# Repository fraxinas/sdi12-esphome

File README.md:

# SDI-12 Interface for ESPHome

(CC) 2023 by Andreas Frisch <github@fraxinas.dev>

## OwO what's this?
**`sdi12-esphome` is an ESP32-based interface for connecting professional meteorologic sensors with ESPHome and Home Assistant**

## Hardware Features
* Based on a NodeMCU ESP32 Module
* 4x SDI-12 inputs via push-in terminals
* Step-up conversion for the 12V SDI-12 sensor power
* Transient surge protection for the SDI-12 data bus
* PCB fits into a BOPLA 100x100mm IP65 case

## Software Features
* Home Assistant intergration using ESPHome.io

## Custom Components
### SDI-12 Bus
* is a wrapper around the https://github.com/EnviroDIY/Arduino-SDI-12 library, with the https://github.com/RAKWireless/RAK13010-SDI12/ modifications to split input, output and enable into separate GPIOs
* allows configuring an SDI-12 Bus component that sensors can be attached to
* configure RX, TX & OE pins through configuration YAML
* provide address scan method

### CS215
* Campbell Scientific CS215 Temperature and Relative Humidity Probe
* https://s.campbellsci.com/documents/ca/manuals/cs215_man.pdf

### DS2
* Decagon Devices DS-2 Sonic Anemometer
* https://library.metergroup.com/Manuals/14586_DS2_Web.pdf
* Sensors for
  * wind speed
  * wind direction
  * wind temperature

### TODOs
- [ ] SDI-12 Bus component (feature complete & tests)
- [ ] Themometer/Hygrometer (feature complete & tests)
- [ ] Anemometer (feature complete & tests)
- [ ] Rain Gauge (start)
- [ ] Generic Sensor (start)
- [ ] Documentation / Photos

## Project Diary
| Date       | Version | Milestone                                        |
| :--------- | :------ | :----------------------------------------------- |
| 2023-10-22 |         | Started Project on the breadboard                |
| 2023-11-06 |         | First successful sensor readout in EPSHome       |
| 2023-11-13 |  v0.1   | Order prototype design at JLCPCB                 |

## Resources
* https://www.sdi-12.org/current_specification/SDI-12_version-1_4-Jan-10-2019.pdf
* https://ww1.microchip.com/downloads/en/DeviceDoc/20005315B.pdf

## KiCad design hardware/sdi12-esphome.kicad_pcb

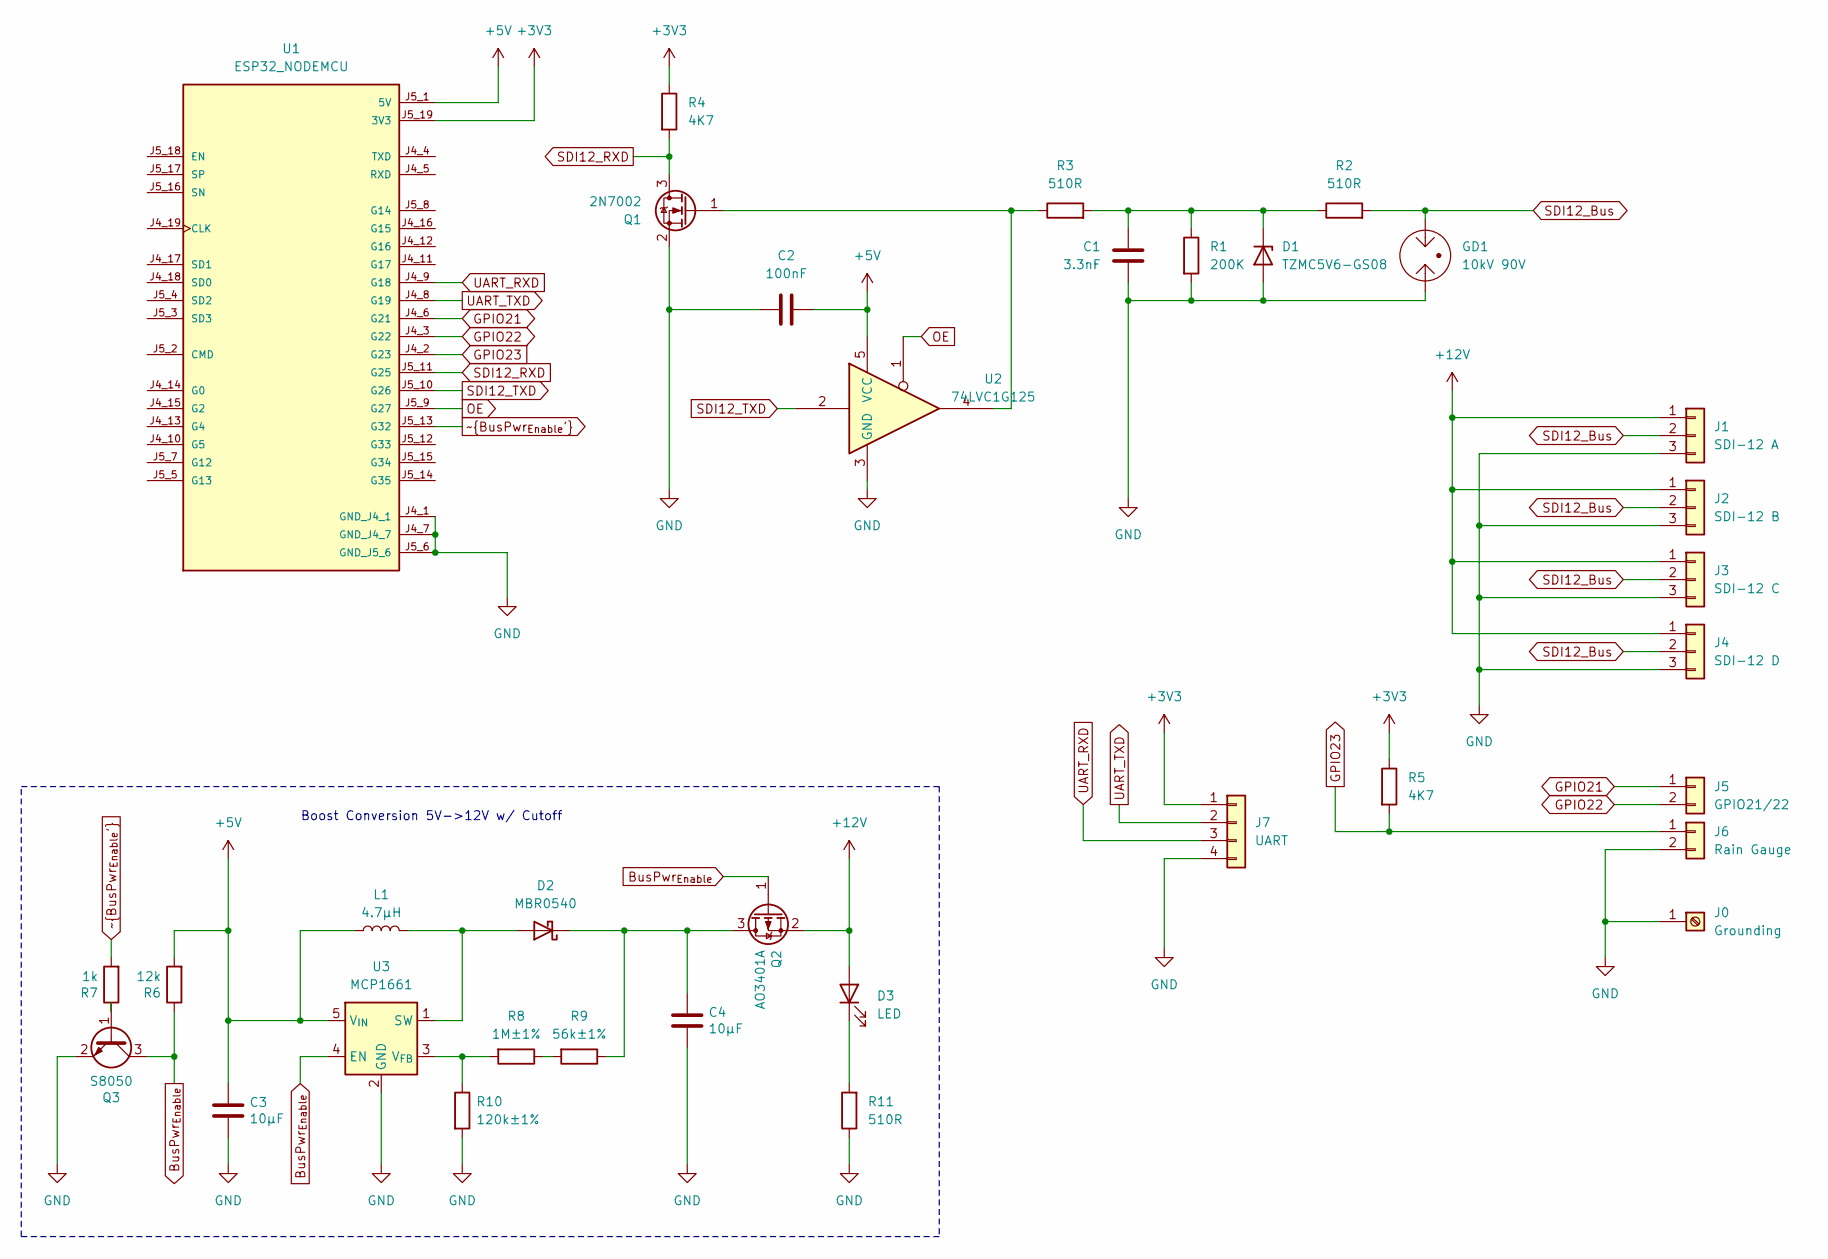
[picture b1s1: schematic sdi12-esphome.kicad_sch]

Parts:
C1: 3.3nF; C_0805_2012Metric_Pad1.18x1.45mm_HandSolder
C2: 100nF; C_0805_2012Metric_Pad1.18x1.45mm_HandSolder
C3, C4: 10µF; C_0805_2012Metric_Pad1.18x1.45mm_HandSolder
D1: TZMC5V6-GS08; D_MiniMELF
D2: MBR0540; D_SOD-123
D3: LED; LED_0805_2012Metric_Pad1.15x1.40mm_HandSolder
GD1: 10kV 90V; Gas Discharge Tube Generic 12.7mm THT
J0: Grounding; MountingHole_4.3mm_M4_ISO7380_Pad_TopBottom
J1: SDI-12 A; Phoenix Contact SPTA 1 3 5,0 1752227
J2: SDI-12 B; Phoenix Contact SPTA 1 3 5,0 1752227
J3: SDI-12 C; Phoenix Contact SPTA 1 3 5,0 1752227
J4: SDI-12 D; Phoenix Contact SPTA 1 3 5,0 1752227
J5: GPIO21/22; Phoenix Contact SPTA 1 2 5,0 1752214
J6: Rain Gauge; Phoenix Contact SPTA 1 2 5,0 1752214
J7: UART; PinSocket_1x04_P2.54mm_Vertical
L1: 4.7µH; L_1008_2520Metric_Pad1.43x2.20mm_HandSolder
Q1: 2N7002; SOT-23
Q2: AO3401A; SOT-23
Q3: S8050; SOT-23
R1: 200K; R_0805_2012Metric_Pad1.20x1.40mm_HandSolder
R2, R3, R11: 510R; R_0805_2012Metric_Pad1.20x1.40mm_HandSolder
R4, R5: 4K7; R_0805_2012Metric_Pad1.20x1.40mm_HandSolder
R6: 12k; R_0805_2012Metric_Pad1.20x1.40mm_HandSolder
R7: 1k; R_0805_2012Metric_Pad1.20x1.40mm_HandSolder
R8: 1M±1%; R_0805_2012Metric_Pad1.20x1.40mm_HandSolder
R9: 56k±1%; R_0805_2012Metric_Pad1.20x1.40mm_HandSolder
R10: 120k±1%; R_0805_2012Metric_Pad1.20x1.40mm_HandSolder
U1: ESP32_NODEMCU; MODULE_ESP32_NODEMCU
U2: 74LVC1G125; SOT-23-5_HandSoldering
U3: MCP1661; SOT-23-5_HandSoldering

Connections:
+3V3: J7.1, R4.1, R5.1, U1.J5_19 (3V3)
+5V: C2.2, C3.1, L1.1, R6.2, U1.J5_1 (5V), U2.5 (VCC), U3.5 (V_{IN})
+12V: D3.2 (A), J1.1, J2.1, J3.1, J4.1, Q2.2 (S)
BusPwr_{Enable}: Q2.1 (G), Q3.3 (C), R6.1, U3.4 (EN)
GND: C1.2, C2.1, C3.2, C4.2, D1.2 (A), GD1.1, J0.1, J1.3, J2.3, J3.3, J4.3, J6.2, J7.4, Q1.2 (S), Q3.2 (E), R1.2, R10.2, R11.1, U1.J4_1 (GND_J4_1), U1.J4_7 (GND_J4_7), U1.J5_6 (GND_J5_6), U2.3 (GND), U3.2 (GND)
GPIO21: J5.1, U1.J4_6 (G21)
GPIO22: J5.2, U1.J4_3 (G22)
GPIO23: J6.1, R5.2, U1.J4_2 (G23)
unnamed: C1.1, D1.1 (K), R1.1, R2.1, R3.2
unnamed: D2.2 (A), L1.2, U3.1 (SW)
unnamed: C4.1, D2.1 (K), Q2.3 (D), R9.1
unnamed: D3.1 (K), R11.2
unnamed: Q1.1 (G), R3.1, U2.4
unnamed: Q3.1 (B), R7.1
unnamed: R8.1, R9.2
unnamed: R8.2, R10.1, U3.3 (V_{FB})
OE: U1.J5_9 (G27), U2.1
SDI12_Bus: GD1.3, J1.2, J2.2, J3.2, J4.2, R2.2
SDI12_RXD: Q1.3 (D), R4.2, U1.J5_11 (G25)
SDI12_TXD: U1.J5_10 (G26), U2.2
UART_RXD: J7.3, U1.J4_9 (G18)
UART_TXD: J7.2, U1.J4_8 (G19)
~BusPwr_{Enable'}: R7.2, U1.J5_13 (G32)

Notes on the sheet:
Boost Conversion 5V->12V w/ Cutoff

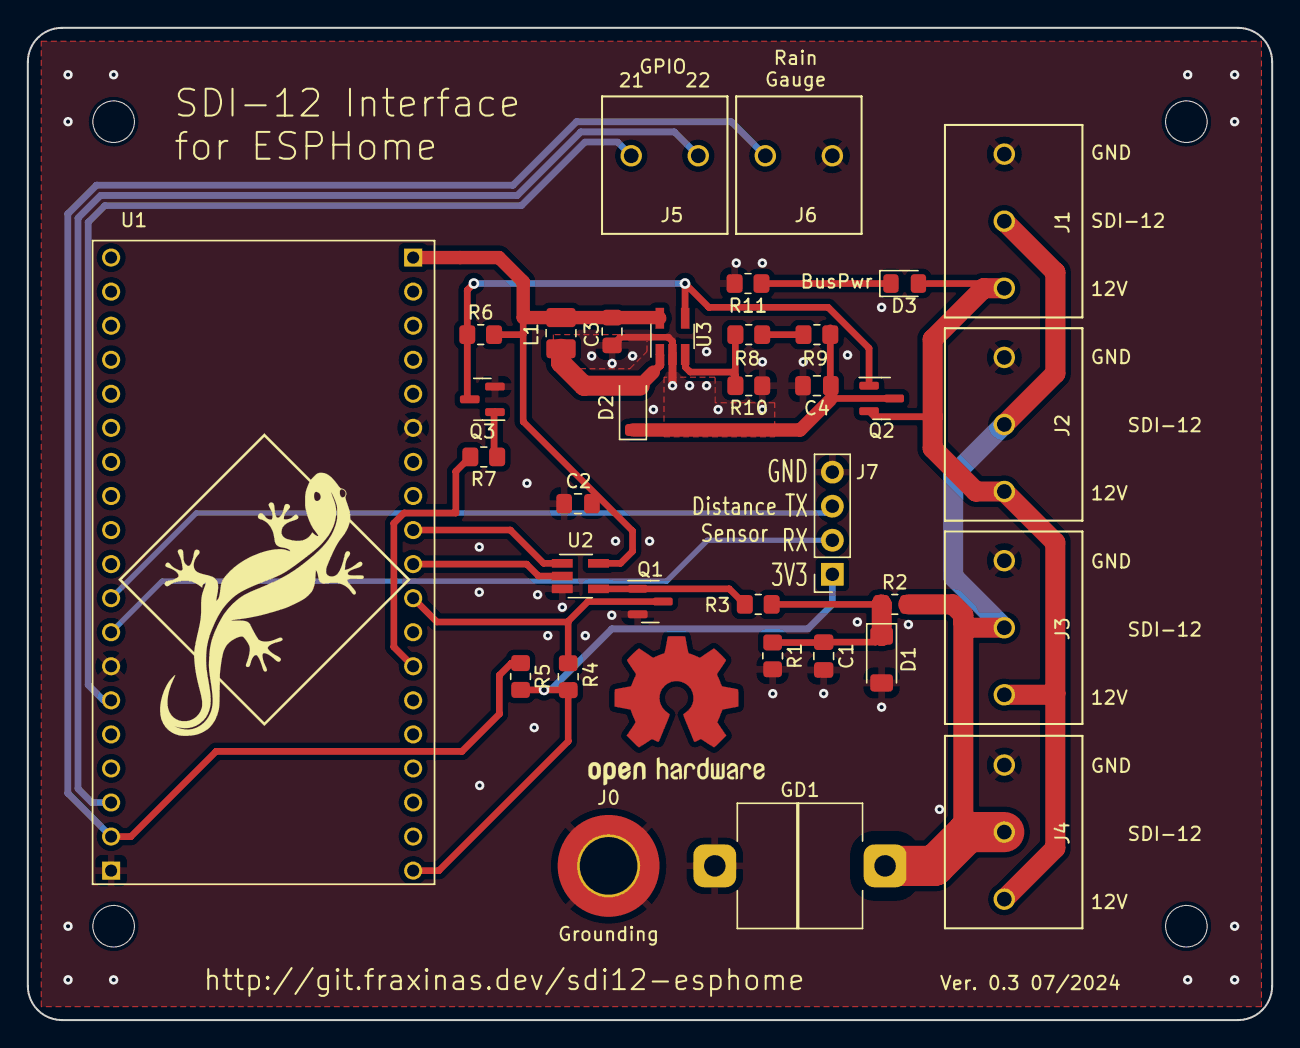
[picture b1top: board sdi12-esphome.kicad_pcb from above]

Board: 2 copper layers, 92.8 x 74.0 mm, 35 parts (0 on the bottom side), 23 nets.

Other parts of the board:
LOGO1: Logo_Open_Hardware_Small; OSHW-Logo2_14.6x12mm_Mask

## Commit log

2023-10-28 gitignore: Ignore local cache and backup files
2023-10-29 schematic: Fix GND Net name, import project settings (trace widths etc.)
2023-10-30 initial commit: Add KiCAD project with basic schematic
2023-10-30 Schematic: Add 12V boost converter for sensor power
2023-10-30 schematic: Add BUS terminals, fixup global labels
2023-10-30 board: Add initial version of PCB layout
2023-10-30 board: Resize Board to fit Case, add Silkscreen Descriptions & Artwork
    * Fits into BOPLA EM 212 (62212000) 100x100 mm Case
2023-10-31 readme: Add Readme
2023-11-01 hardware: Move KiCAD files into hardware subdir
2023-11-02 Software: Add Platform.io test project for scanning the SDI-12 bus
2023-11-02 software: Add skeleton SDI12 custom component for ESPHome
    * based on https://github.com/RAKWireless/RAK13010-SDI12/tree/main
2023-11-02 Software: Add sdi12.yaml ESPHome configuration file
2023-11-02 Software: Add .gitignore for secrets and generated files
2023-11-02 sdi12: Add SDI12Device and SDI12Register classes
2023-11-02 sdi12: Change SDI-12 address type & validator, remove logger
2023-11-02 ds2: Add DS2 Sensor component dummy
2023-11-02 Software: Add DS2 test sensor to configuration
2023-11-03 ds2: Add wind direction and temperature sensors & implement update function
2023-11-04 sdi12: Add missing implementation for Timer Prescaler functions
    * These are NOP for anything non-AVR anyways
2023-11-04 sdi12: Implement bus scan and activity check
2023-11-04 sdi12: Work on test application
    * Make Pin setup consistent with ESPHome component
    * Add function which finds the necessary individual delay for a SDI-12 device
2023-11-05 sdi1: Work on test application, tweak timing
    With the CS215 sensor, timing is absolutely crucial
    Found the only working sequence of requesting address from it
2023-11-05 sdi12: Implement address validation and fix address type & setter
2023-11-05 cs215: Add skeleton SDI-12 Humidity & Temperature Probe CS 215
2023-11-05 sdi12: Implement send_command method
2023-11-05 software: Add CS215 test component, disable SDI12 bus scan
2023-11-05 sdi12: Add query measurement of CS-215 to test application
2023-11-05 sdi12: Fix send_command method
    * add missing begin() and end() calls
2023-11-05 cs215: Add timed data request function
    * this properly receives the sensor data (temperature and humidity)
    * parsing TBD
2023-11-06 sdi12: Remove remaining AVR handling from lib
2023-11-06 sdi12: Add parser function that can parse a variable amount of float values from a data response
2023-11-06 ds2: Use SDI12 Component method to parse values from data responses
2023-11-06 CS215: Use SDI12 Component method to parse values from data responses
2023-11-06 SDI12: Perform sinlge bus address scans in loop function
    * This avoids tripping the watchdog timer
2023-11-06 sdi12/cs215: Fix parsing the last value
    * remove trailing line endings from string before conversion
    * don't NAN out if !EOF
    * show results with full precision
2023-11-06 sdi12: Improve scanning
    * Refactor into more consistent methods
    * Fix result parsing and display
    * Provide is_scanning() check
2023-11-06 cs215+ds2: Fix data acquisition
    * Don't update during scanning
    * Fix data response handlers
2023-11-07 hardware: Rename and fix footprints and 3D assets for Terminals
2023-11-07 Schematic: Add additional GPIO and Rain Gauge ports, re-arrange schematic elements
2023-11-07 board: Add additional GPIO and Rain Gauge ports, re-arrange PCB elements
2023-11-07 hardware: Add 3D model for 2x Terminal
2023-11-07 software: Add DS2 Windtemperature and Winddirection sensors to config
2023-11-07 hardware: Move & append .gitignore
2023-11-07 Hardware: Add PCB 3D rendering
2023-11-07 hardware: Add Schematic PDF
2023-11-08 Readme: Add Custom components' descriptions & PCB rendering
2023-11-09 hardware: Fix Terminals' footprints
    Move Silkscreen prints away from pads (DRC rule)
2023-11-09 hardware: Add dedicated footprint for Gas Discharge Tube
    * using the diode one was confusing the DRC
2023-11-09 schematic: Add Bus Power indicator LED, use GD footprint, fix terminal mod
2023-11-09 board: Implement LED, re-arrange snubber and boost converter
    * also fix some DRC problems
2023-11-13 hardware: Add Aisler's sesign rules definition
2023-11-13 board: Import Aisler's simple board properties
2023-11-13 board: Update all Vias to spec
2023-11-13 library: Remove DRC conflicting solder_mask_margin from NodeMCU footprint
2023-11-13 board: Fix DRC errors (trace min spacing undercuts)
2023-11-14 gerber: Export manufacturing data
2023-11-15 readme: Update project diary
2023-11-24 Schematic: Add P-MOSFET for power cutoff
2023-11-25 Board: Layout for power cut-off MOSFET
2023-11-26 Library: Use correct dimensions for AI-Thinker NODEMCU-32 V1.2
2023-11-26 Schematic: Add additional NPN for level shifting the BusPwrEnable signal
2023-12-12 CS215/ds12: Fix parser to work with negative values
2024-07-14 Add Header for RCWL-1655 Distance Sensor Module
2024-07-14 Add custom component for reading out RCWL-1655 Distance sensors for cistern filling level
